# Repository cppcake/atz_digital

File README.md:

# atz_digital
Dateien zu meiner Bachelorarbeit - only avaible in german

Für mehr Infos siehe README in `./hardware` und `./software`.

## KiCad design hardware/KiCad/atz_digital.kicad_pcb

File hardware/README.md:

# ATZ-Digital Hardware
Hier ist alles Hardware-related, dass ich in meiner Bachelorarbeit zur Digitalisierung einer Therapie für Menschen im Autismus-Spektrum verwendet habe. Darunter insbesondere die 3D-Modelle, die Leiterplatte und der Quellcode für die ESP's.

## Danksagung
Einen riesen Dank an @MayNiklas für die intensive Beratung und Arbeit an der Leiterplatte, dem 3D-Design, der Hardwareauswahl, dem Zusammenbauen der Bauteile und vielem mehr!

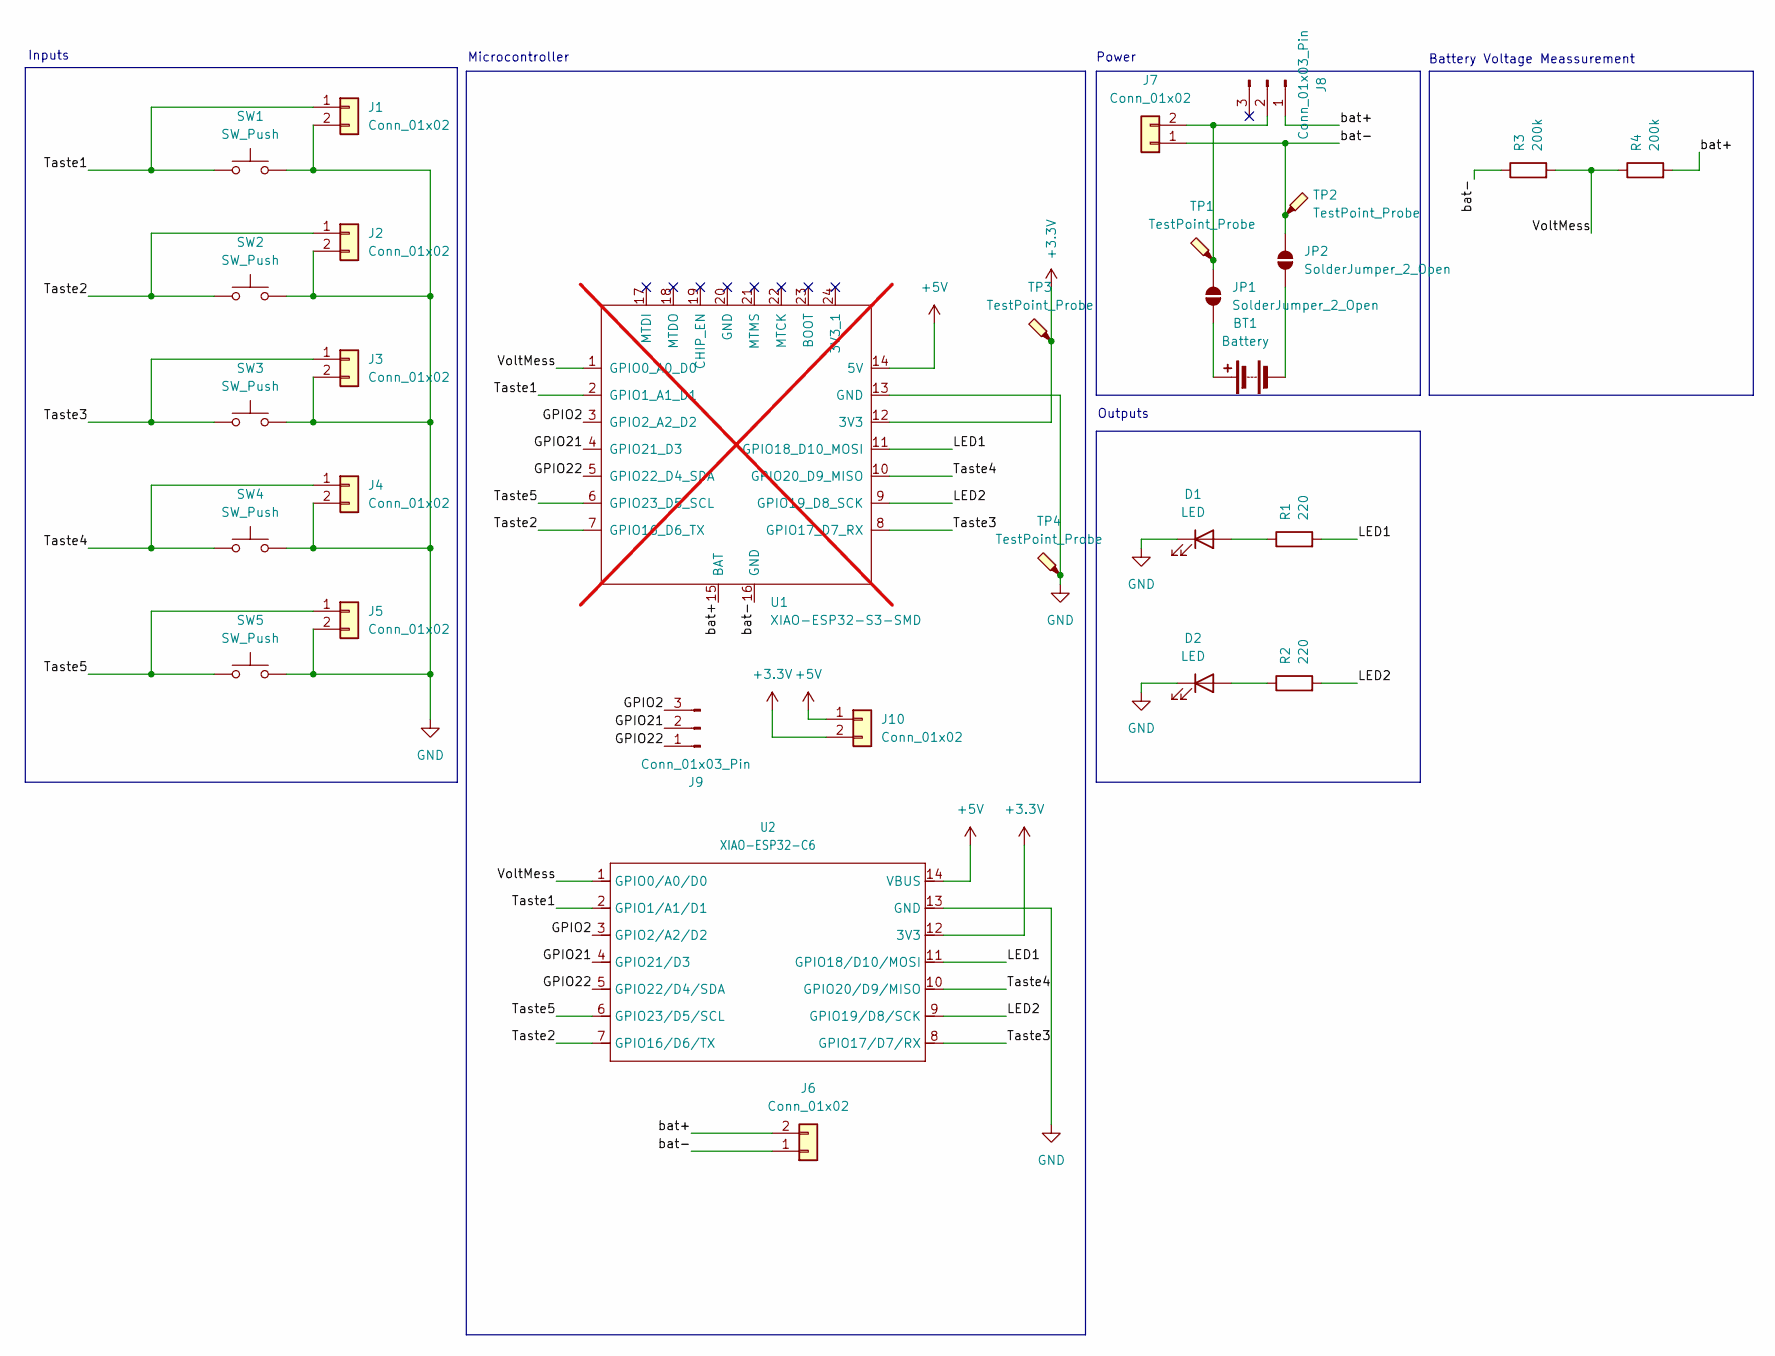
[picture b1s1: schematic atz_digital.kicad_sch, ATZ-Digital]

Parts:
BT1: Battery; BatteryHolder_Keystone_1042_1x18650; LCSC C2988620
D1, D2: LED; JST_XH_B2B-XH-A_1x02_P2.50mm_Vertical; LCSC C158012
J1, J2, J3, J4, J5, J6, J7: Conn_01x02; JST_XH_B2B-XH-A_1x02_P2.50mm_Vertical; LCSC C158012
J8, J9: Conn_01x03_Pin; PinHeader_1x03_P2.54mm_Vertical
J10: Conn_01x02; PinHeader_1x02_P2.54mm_Vertical
JP1, JP2: SolderJumper_2_Open; SolderJumper-2_P1.3mm_Open_RoundedPad1.0x1.5mm
R1, R2: 220; R_0805_2012Metric; LCSC C17557
R3, R4: 200k; R_0805_2012Metric; LCSC C17539
SW1, SW2, SW3, SW4, SW5: SW_Push; SW-TH_4P-L6.0-W6.0-P4.50-LS6.5; LCSC C393938
TP1, TP2, TP3, TP4: TestPoint_Probe; TestPoint_THTPad_D2.5mm_Drill1.2mm
U1: XIAO-ESP32-S3-SMD; XIAO-ESP32C6-SMD; not fitted
U2: XIAO-ESP32-C6; XIAO-ESP32C6-DIP

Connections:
+3.3V: J10.2, TP3.1, U1.12 (3V3), U2.12 (3V3)
+5V: J10.1, U1.14 (5V), U2.14 (VBUS)
/GPIO2: J9.3, U1.3 (GPIO2_A2_D2), U2.3 (GPIO2/A2/D2)
/GPIO21: J9.2, U1.4 (GPIO21_D3), U2.4 (GPIO21/D3)
/GPIO22: J9.1, U1.5 (GPIO22_D4_SDA), U2.5 (GPIO22/D4/SDA)
/LED1: R1.2, U1.11 (GPIO18_D10_MOSI), U2.11 (GPIO18/D10/MOSI)
/LED2: R2.2, U1.9 (GPIO19_D8_SCK), U2.9 (GPIO19/D8/SCK)
/Taste1: J1.1, SW1.1, U1.2 (GPIO1_A1_D1), U2.2 (GPIO1/A1/D1)
/Taste2: J2.1, SW2.1, U1.7 (GPIO16_D6_TX), U2.7 (GPIO16/D6/TX)
/Taste3: J3.1, SW3.1, U1.8 (GPIO17_D7_RX), U2.8 (GPIO17/D7/RX)
/Taste4: J4.1, SW4.1, U1.10 (GPIO20_D9_MISO), U2.10 (GPIO20/D9/MISO)
/Taste5: J5.1, SW5.1, U1.6 (GPIO23_D5_SCL), U2.6 (GPIO23/D5/SCL)
/VoltMess: R3.2, R4.1, U1.1 (GPIO0_A0_D0), U2.1 (GPIO0/A0/D0)
/bat+: J6.2, J8.1, R4.2, U1.15 (BAT)
/bat-: J6.1, J7.1, JP2.2 (B), R3.1, TP2.1, U1.16 (GND)
GND: D1.1 (K), D2.1 (K), J1.2, J2.2, J3.2, J4.2, J5.2, SW1.2, SW2.2, SW3.2, SW4.2, SW5.2, TP4.1, U1.13 (GND), U2.13 (GND)
unnamed: BT1.1 (+), JP1.1 (A)
unnamed: BT1.2 (-), JP2.1 (A)
unnamed: D1.2 (A), R1.1
unnamed: D2.2 (A), R2.1
unnamed: J7.2, J8.2, JP1.2 (B), TP1.1

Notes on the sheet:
Battery Voltage Meassurement
Power
Outputs
Inputs
Microcontroller

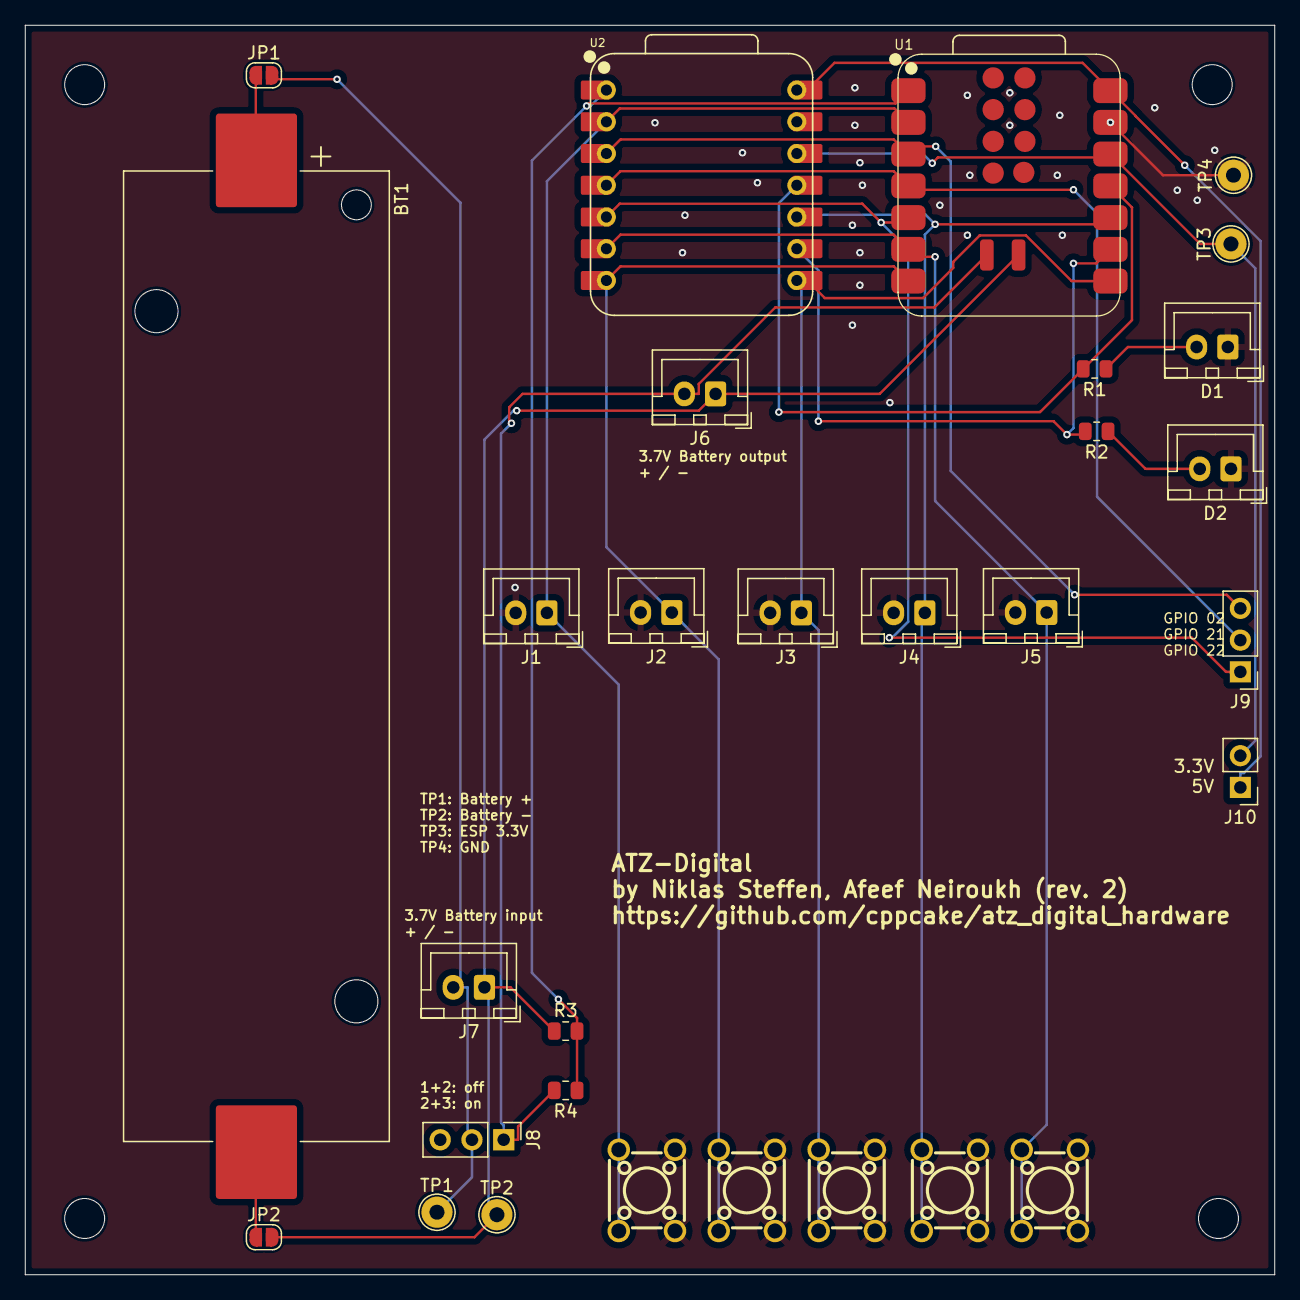
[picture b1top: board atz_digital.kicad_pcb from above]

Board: 2 copper layers, 100.0 x 100.0 mm, 34 parts (0 on the bottom side), 21 nets.

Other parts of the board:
H1, H2, H3, H4: MountingHole_3.2mm_M3

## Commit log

2025-10-27 Init
2025-10-27 Refactor
2025-10-30 Init 2
